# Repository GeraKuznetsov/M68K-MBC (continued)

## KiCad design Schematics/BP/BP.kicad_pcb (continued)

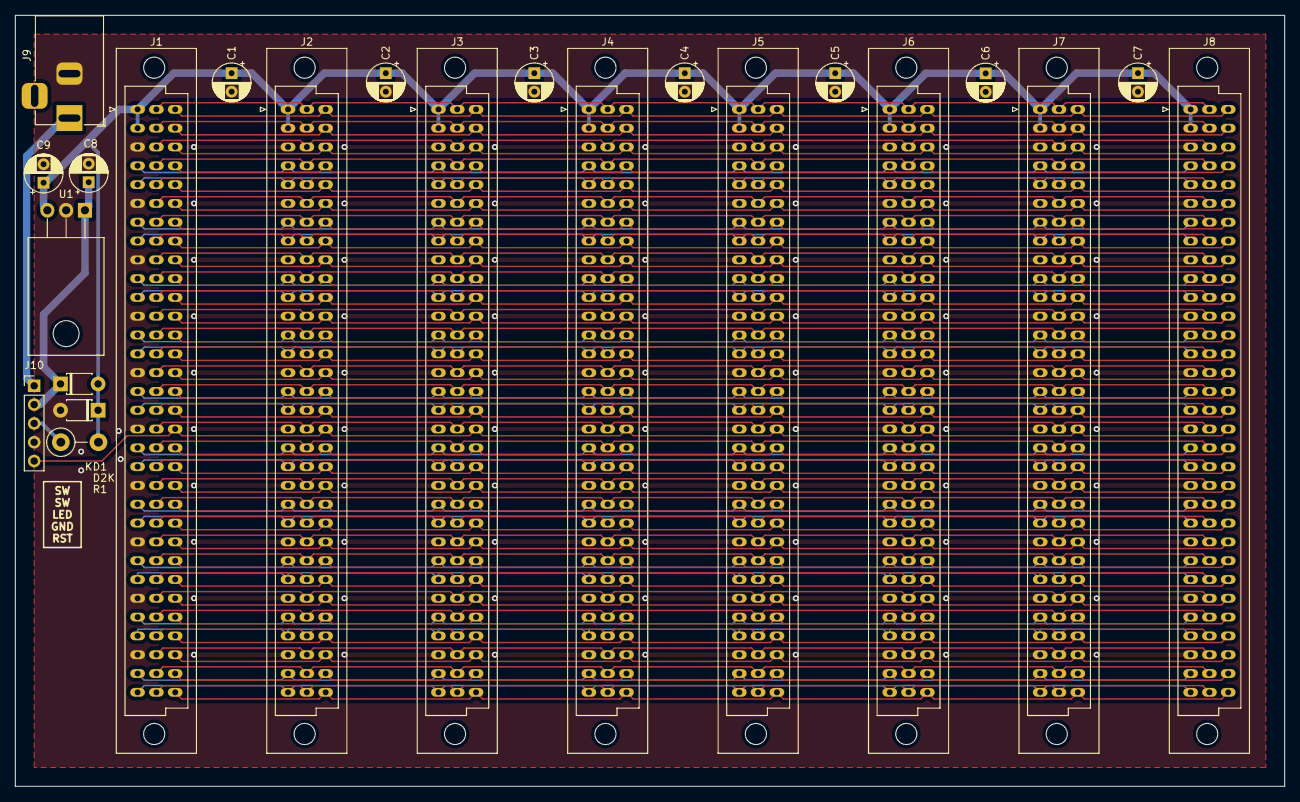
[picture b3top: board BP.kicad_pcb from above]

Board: 2 copper layers, 171.4 x 104.1 mm, 23 parts (0 on the bottom side), 89 nets.

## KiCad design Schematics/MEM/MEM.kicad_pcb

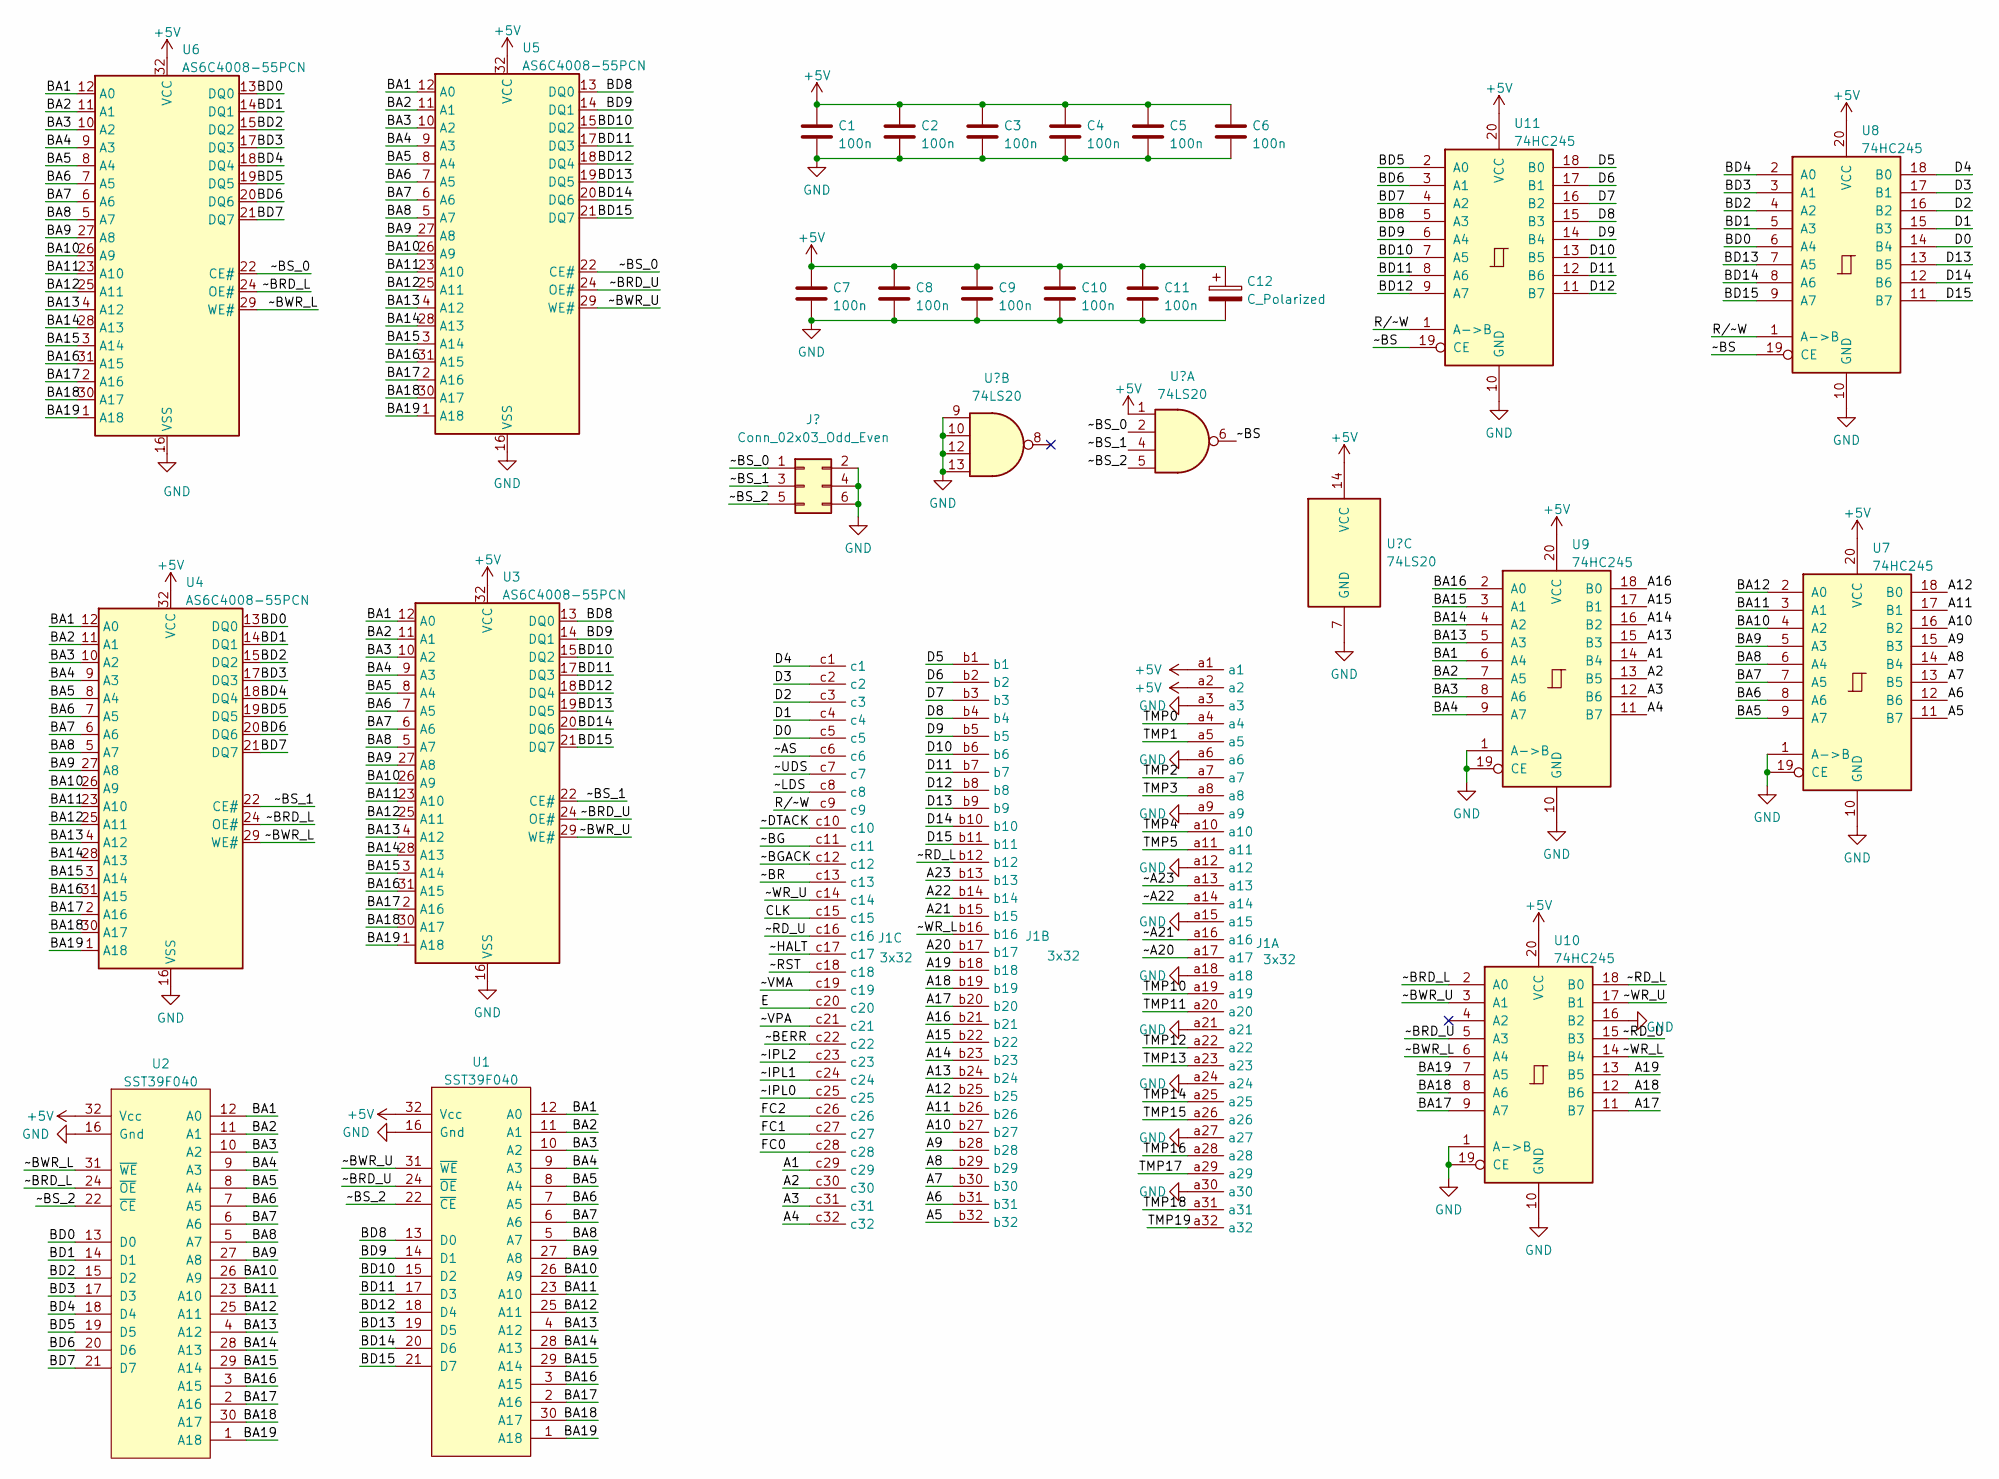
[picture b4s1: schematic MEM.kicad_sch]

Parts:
C1, C2, C3, C4, C5, C6, C7, C8, C9, C10, C11: 100n; DIP-2_200_ELL
C12: C_Polarized; CP_Radial_D4.0mm_P1.50mm
J1: 3x32; DIN41612_R_3x32_Male_Horizontal_THT
U1, U2: SST39F040; DIP-32_600_ELL
U3, U4, U5, U6: AS6C4008-55PCN; DIP-32_600_ELL
U7, U8, U9, U10, U11: 74HC245; DIP-20

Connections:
+5V: C1.1, C2.1, C3.1, C4.1, C5.1, C6.1, C7.1, C8.1, C9.1, C10.1, C11.1, C12.1, J1.a1, J1.a2, U1.32 (Vcc), U2.32 (Vcc), U3.32 (VCC), U4.32 (VCC), U5.32 (VCC), U6.32 (VCC), U7.20 (VCC), U8.20 (VCC), U9.20 (VCC), U10.20 (VCC), U11.20 (VCC)
/A1: J1.c29, U9.14 (B4)
/A2: J1.c30, U9.13 (B5)
/A3: J1.c31, U9.12 (B6)
/A4: J1.c32, U9.11 (B7)
/A5: J1.b32, U7.11 (B7)
/A6: J1.b31, U7.12 (B6)
/A7: J1.b30, U7.13 (B5)
/A8: J1.b29, U7.14 (B4)
/A9: J1.b28, U7.15 (B3)
/A10: J1.b27, U7.16 (B2)
/A11: J1.b26, U7.17 (B1)
/A12: J1.b25, U7.18 (B0)
/A13: J1.b24, U9.15 (B3)
/A14: J1.b23, U9.16 (B2)
/A15: J1.b22, U9.17 (B1)
/A16: J1.b21, U9.18 (B0)
/A17: J1.b20, U10.11 (B7)
/A18: J1.b19, U10.12 (B6)
/A19: J1.b18, U10.13 (B5)
/A20: J1.b17
/A21: J1.b15
/A22: J1.b14
/A23: J1.b13
/BA1: U1.12 (A0), U2.12 (A0), U3.12 (A0), U4.12 (A0), U5.12 (A0), U6.12 (A0), U9.6 (A4)
/BA2: U1.11 (A1), U2.11 (A1), U3.11 (A1), U4.11 (A1), U5.11 (A1), U6.11 (A1), U9.7 (A5)
/BA3: U1.10 (A2), U2.10 (A2), U3.10 (A2), U4.10 (A2), U5.10 (A2), U6.10 (A2), U9.8 (A6)
/BA4: U1.9 (A3), U2.9 (A3), U3.9 (A3), U4.9 (A3), U5.9 (A3), U6.9 (A3), U9.9 (A7)
/BA5: U1.8 (A4), U2.8 (A4), U3.8 (A4), U4.8 (A4), U5.8 (A4), U6.8 (A4), U7.9 (A7)
/BA6: U1.7 (A5), U2.7 (A5), U3.7 (A5), U4.7 (A5), U5.7 (A5), U6.7 (A5), U7.8 (A6)
/BA7: U1.6 (A6), U2.6 (A6), U3.6 (A6), U4.6 (A6), U5.6 (A6), U6.6 (A6), U7.7 (A5)
/BA8: U1.5 (A7), U2.5 (A7), U3.5 (A7), U4.5 (A7), U5.5 (A7), U6.5 (A7), U7.6 (A4)
/BA9: U1.27 (A8), U2.27 (A8), U3.27 (A8), U4.27 (A8), U5.27 (A8), U6.27 (A8), U7.5 (A3)
/BA10: U1.26 (A9), U2.26 (A9), U3.26 (A9), U4.26 (A9), U5.26 (A9), U6.26 (A9), U7.4 (A2)
/BA11: U1.23 (A10), U2.23 (A10), U3.23 (A10), U4.23 (A10), U5.23 (A10), U6.23 (A10), U7.3 (A1)
/BA12: U1.25 (A11), U2.25 (A11), U3.25 (A11), U4.25 (A11), U5.25 (A11), U6.25 (A11), U7.2 (A0)
/BA13: U1.4 (A12), U2.4 (A12), U3.4 (A12), U4.4 (A12), U5.4 (A12), U6.4 (A12), U9.5 (A3)
/BA14: U1.28 (A13), U2.28 (A13), U3.28 (A13), U4.28 (A13), U5.28 (A13), U6.28 (A13), U9.4 (A2)
/BA15: U1.29 (A14), U2.29 (A14), U3.3 (A14), U4.3 (A14), U5.3 (A14), U6.3 (A14), U9.3 (A1)
/BA16: U1.3 (A15), U2.3 (A15), U3.31 (A15), U4.31 (A15), U5.31 (A15), U6.31 (A15), U9.2 (A0)
/BA17: U1.2 (A16), U2.2 (A16), U3.2 (A16), U4.2 (A16), U5.2 (A16), U6.2 (A16), U10.9 (A7)
/BA18: U1.30 (A17), U2.30 (A17), U3.30 (A17), U4.30 (A17), U5.30 (A17), U6.30 (A17), U10.8 (A6)
/BA19: U1.1 (A18), U2.1 (A18), U3.1 (A18), U4.1 (A18), U5.1 (A18), U6.1 (A18), U10.7 (A5)
/BD0: U2.13 (D0), U4.13 (DQ0), U6.13 (DQ0), U8.6 (A4)
/BD1: U2.14 (D1), U4.14 (DQ1), U6.14 (DQ1), U8.5 (A3)
/BD2: U2.15 (D2), U4.15 (DQ2), U6.15 (DQ2), U8.4 (A2)
/BD3: U2.17 (D3), U4.17 (DQ3), U6.17 (DQ3), U8.3 (A1)
/BD4: U2.18 (D4), U4.18 (DQ4), U6.18 (DQ4), U8.2 (A0)
/BD5: U2.19 (D5), U4.19 (DQ5), U6.19 (DQ5), U11.2 (A0)
/BD6: U2.20 (D6), U4.20 (DQ6), U6.20 (DQ6), U11.3 (A1)
/BD7: U2.21 (D7), U4.21 (DQ7), U6.21 (DQ7), U11.4 (A2)
/BD8: U1.13 (D0), U3.13 (DQ0), U5.13 (DQ0), U11.5 (A3)
/BD9: U1.14 (D1), U3.14 (DQ1), U5.14 (DQ1), U11.6 (A4)
/BD10: U1.15 (D2), U3.15 (DQ2), U5.15 (DQ2), U11.7 (A5)
/BD11: U1.17 (D3), U3.17 (DQ3), U5.17 (DQ3), U11.8 (A6)
/BD12: U1.18 (D4), U3.18 (DQ4), U5.18 (DQ4), U11.9 (A7)
/BD13: U1.19 (D5), U3.19 (DQ5), U5.19 (DQ5), U8.7 (A5)
/BD14: U1.20 (D6), U3.20 (DQ6), U5.20 (DQ6), U8.8 (A6)
/BD15: U1.21 (D7), U3.21 (DQ7), U5.21 (DQ7), U8.9 (A7)
/CLK: J1.c15
/D0: J1.c5, U8.14 (B4)
/D1: J1.c4, U8.15 (B3)
/D2: J1.c3, U8.16 (B2)
/D3: J1.c2, U8.17 (B1)
/D4: J1.c1, U8.18 (B0)
/D5: J1.b1, U11.18 (B0)
/D6: J1.b2, U11.17 (B1)
/D7: J1.b3, U11.16 (B2)
/D8: J1.b4, U11.15 (B3)
/D9: J1.b5, U11.14 (B4)
/D10: J1.b6, U11.13 (B5)
/D11: J1.b7, U11.12 (B6)
/D12: J1.b8, U11.11 (B7)
/D13: J1.b9, U8.13 (B5)
/D14: J1.b10, U8.12 (B6)
/D15: J1.b11, U8.11 (B7)
/E: J1.c20
/FC0: J1.c28
/FC1: J1.c27
/FC2: J1.c26
/R/~W: J1.c9, U8.1 (A->B), U11.1 (A->B)
/TMP0: J1.a4
/TMP1: J1.a5
/TMP2: J1.a7
/TMP3: J1.a8
/TMP4: J1.a10
/TMP5: J1.a11
/TMP10: J1.a19
/TMP11: J1.a20
/TMP12: J1.a22
/TMP13: J1.a23
/TMP14: J1.a25
/TMP15: J1.a26
/TMP16: J1.a28
/TMP17: J1.a29
/TMP18: J1.a31
/TMP19: J1.a32
/~A20: J1.a17
/~A21: J1.a16
/~A22: J1.a14
/~A23: J1.a13
/~AS: J1.c6
/~BERR: J1.c22
/~BG: J1.c11
/~BGACK: J1.c12
/~BR: J1.c13
/~BRD_L: U2.24 (~OE), U4.24 (OE#), U6.24 (OE#), U10.2 (A0)
/~BRD_U: U1.24 (~OE), U3.24 (OE#), U5.24 (OE#), U10.5 (A3)
/~BS: U8.19 (CE), U11.19 (CE)
/~BS_0: U5.22 (CE#), U6.22 (CE#)
/~BS_1: U3.22 (CE#), U4.22 (CE#)
/~BS_2: U1.22 (~CE), U2.22 (~CE)
/~BWR_L: U2.31 (~WE), U4.29 (WE#), U6.29 (WE#), U10.6 (A4)
/~BWR_U: U1.31 (~WE), U3.29 (WE#), U5.29 (WE#), U10.3 (A1)
/~DTACK: J1.c10
/~HALT: J1.c17
/~IPL0: J1.c25
/~IPL1: J1.c24
/~IPL2: J1.c23
/~LDS: J1.c8
/~RD_L: J1.b12, U10.18 (B0)
/~RD_U: J1.c16, U10.15 (B3)
/~RST: J1.c18
/~UDS: J1.c7
/~VMA: J1.c19
/~VPA: J1.c21
/~WR_L: J1.b16, U10.14 (B4)
/~WR_U: J1.c14, U10.17 (B1)
GND: C1.2, C2.2, C3.2, C4.2, C5.2, C6.2, C7.2, C8.2, C9.2, C10.2, C11.2, C12.2, J1.a3, J1.a6, J1.a9, J1.a12, J1.a15, J1.a18, J1.a21, J1.a24, J1.a27, J1.a30, U1.16 (Gnd), U2.16 (Gnd), U3.16 (VSS), U4.16 (VSS), U5.16 (VSS), U6.16 (VSS), U7.1 (A->B), U7.10 (GND), U7.19 (CE), U8.10 (GND), U9.1 (A->B), U9.10 (GND), U9.19 (CE), U10.1 (A->B), U10.10 (GND), U10.16 (B2), U10.19 (CE), U11.10 (GND)

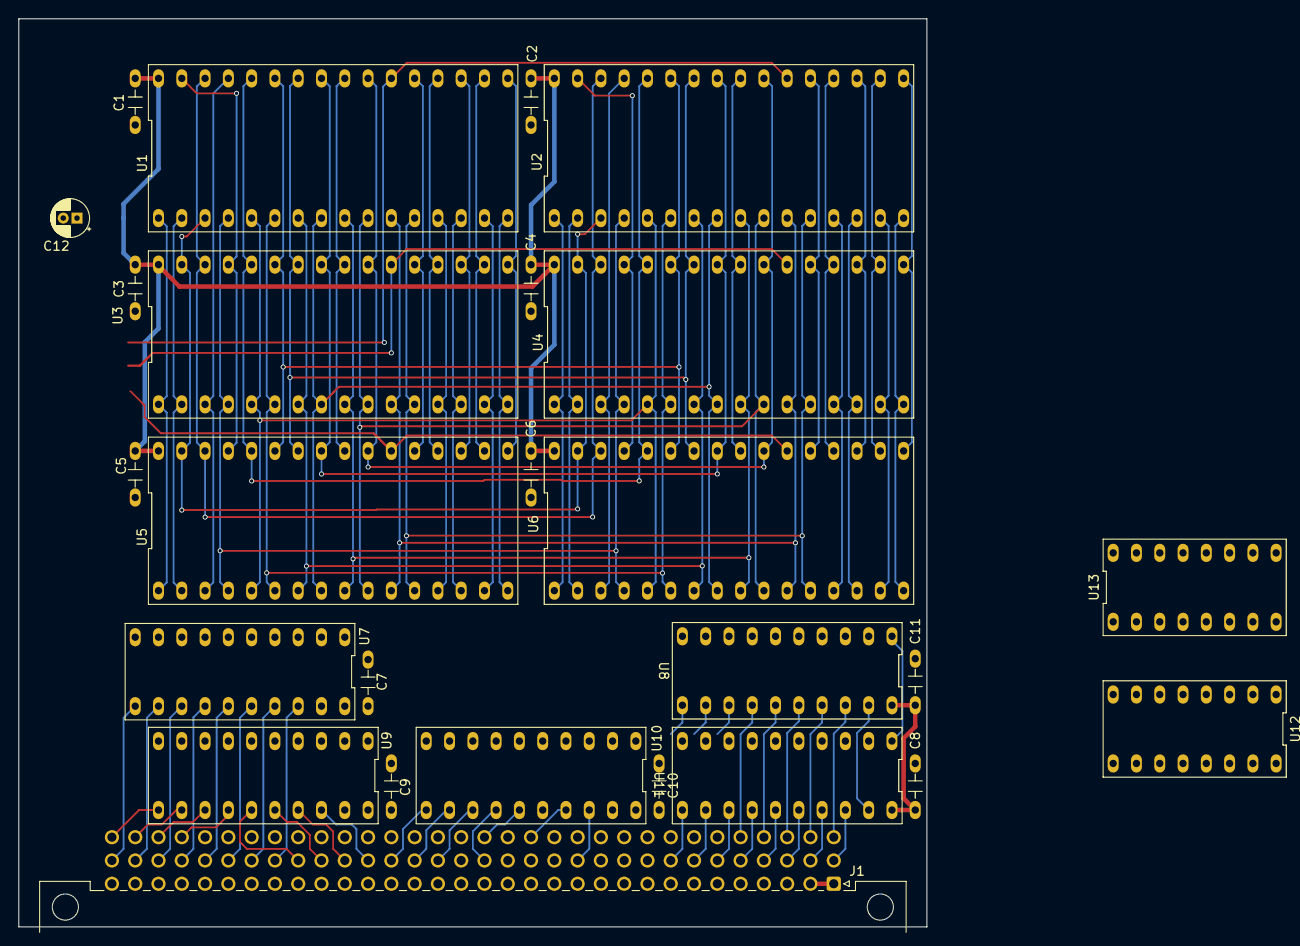
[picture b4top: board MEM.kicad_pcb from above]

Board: 4 copper layers, 99.1 x 99.1 mm, 26 parts (0 on the bottom side), 85 nets.

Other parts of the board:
U12: 74LS85; DIP-16
U13: 74LS138; DIP-16

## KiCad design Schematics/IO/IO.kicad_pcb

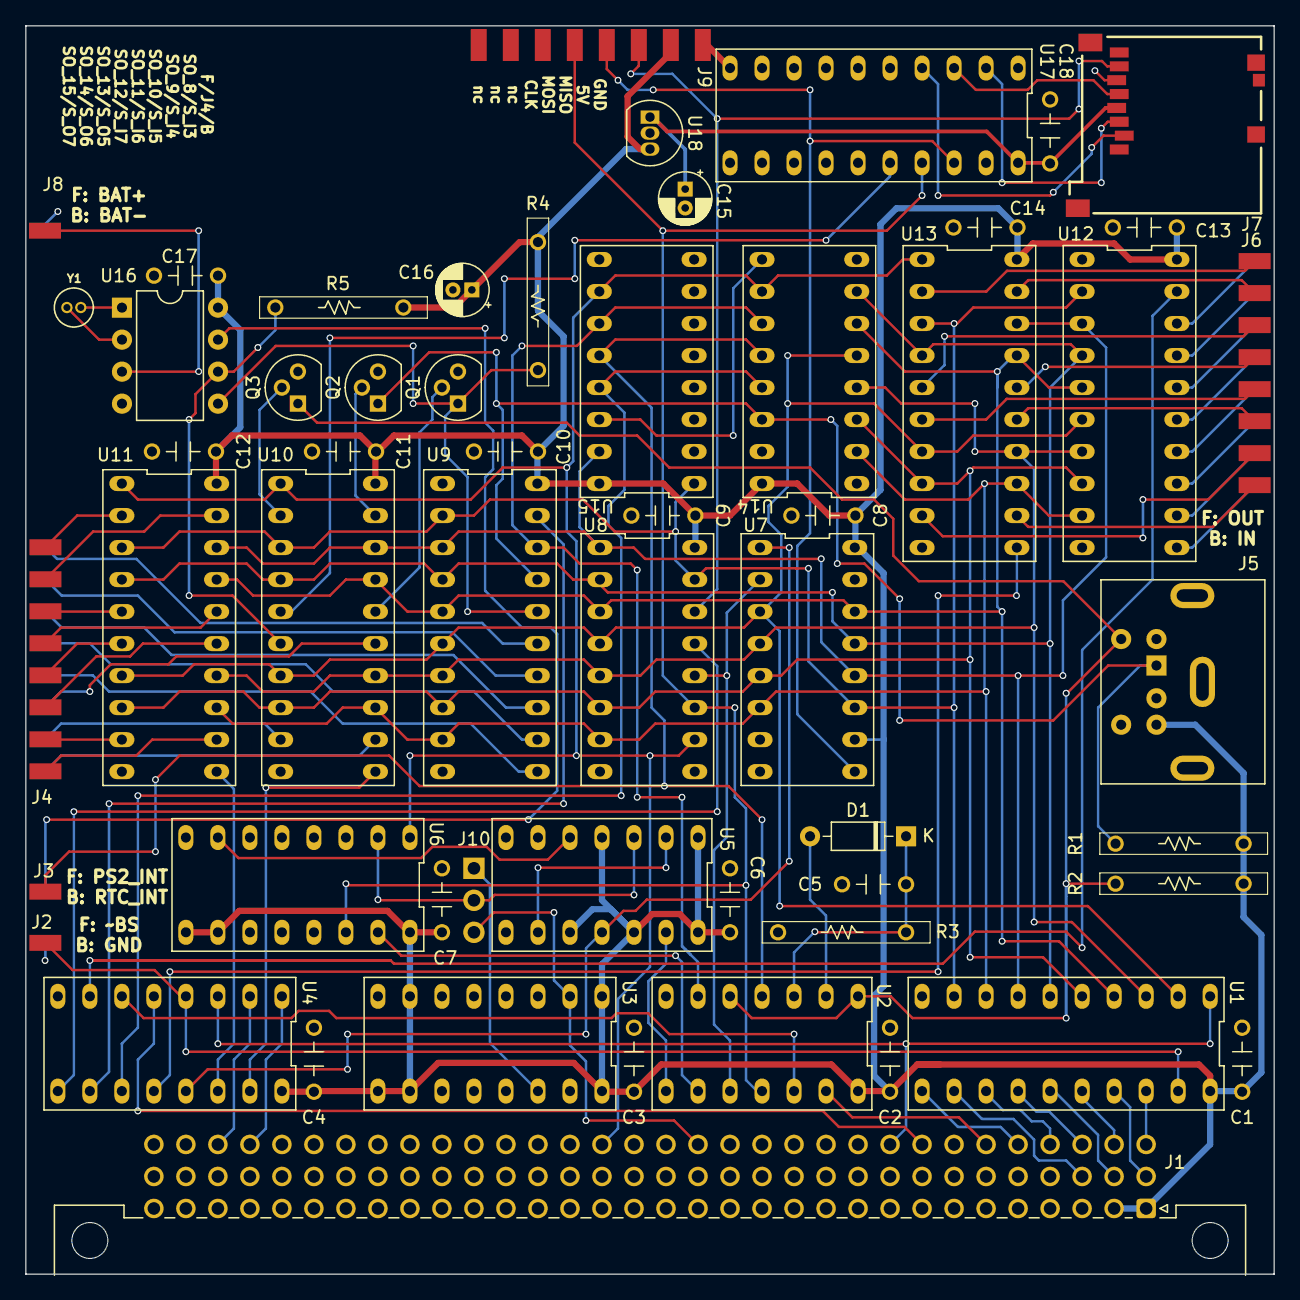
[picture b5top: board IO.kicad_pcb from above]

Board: 4 copper layers, 99.1 x 99.1 mm, 56 parts (0 on the bottom side), 98 nets.

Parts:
C1, C2, C3, C4, C6, C7, C8, C9, C10, C11, C12, C13, C14, C17, C18: 100n; DIP-2_200_ELL
C5: 100nF; DIP-2_200_ELL
C15, C16: C_Polarized; CP_Radial_D4.0mm_P1.50mm
D1: D; D_DO-35_SOD27_P7.62mm_Horizontal
J1: 3x32; DIN41612_R_3x32_Male_Horizontal_THT
J2, J3, J8: 2x01; 2x01 finger
J4: Conn_02x08_Top_Bottom; 2x08 finger
J5: Mini-DIN-6; din
J6: 02x08; 2x08 finger
J7: Micro_SD_Card_Det; sd
J9: 2x08; 2x08 finger
J10: 1x03; PinHeader_1x03_P2.54mm_Vertical
Q1, Q2, Q3: Q_NMOS_DGS; TO-92
R1, R2, R3: 1K; res
R4, R5: R; res
U1, U9, U12: 74HC245; DIP-20
U2: 74HC14; DIP-14
U3, U6: 74LS161; DIP-16
U4: 74LS138; DIP-16
U5: 74HC74; DIP-14
U7: 74HC165; DIP-16
U8, U14, U15: 74HC595; DIP-16
U10, U11, U13: 74HC273; DIP-20
U16: DS1307+; DIP-8_W7.62mm
U17: 74LVC245; DIP-20
U18: LP2950-3.3_TO92; TO-92_Inline
Y1: 32768hz; XTAL_ECS-.327-12.5-8X-C

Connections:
+3V3: C15.1, C18.1, J7.4 (VDD), U17.20 (VCC), U18.1 (VO)
+5V: C1.1, C2.1, C3.1, C4.1, C6.1, C7.1, C8.1, C9.1, C10.1, C11.1, C12.1, C13.1, C14.1, C16.1, C17.1, J1.a1, J1.a2, J5.4, J9.2, R1.1, R2.1, R4.1, R5.1, U1.20 (VCC), U2.14 (VCC), U3.1 (~MR), U3.7 (CEP), U3.9 (~PE), U3.10 (CET), U3.16 (VCC), U4.16 (VCC), U5.1 (~R), U5.4 (~S), U5.10 (~S), U5.12 (D), U5.14 (VCC), U6.9 (~PE), U6.10 (CET), U6.16 (VCC), U7.10 (DS), U7.16 (VCC), U8.16 (VCC), U9.20 (VCC), U10.20 (VCC), U11.20 (VCC), U12.20 (VCC), U13.20 (VCC), U14.16 (VCC), U15.16 (VCC), U16.8 (VCC), U18.3 (VI)
/A1: J1.c29, U4.1 (A0)
/A2: J1.c30, U4.2 (A1)
/BD0: U1.9 (A7), U7.11 (D0), U8.15 (QA), U9.2 (A0), U10.3 (D0), U11.3 (D0), U12.2 (A0), U13.3 (D0), U15.1 (QB)
/BD1: U1.7 (A5), U7.12 (D1), U8.1 (QB), U9.3 (A1), U10.18 (D7), U11.18 (D7), U12.3 (A1), U13.18 (D7), U15.15 (QA)
/BD2: U1.6 (A4), U7.13 (D2), U8.2 (QC), U9.4 (A2), U10.4 (D1), U11.4 (D1), U12.4 (A2), U13.4 (D1), U14.7 (QH)
/BD3: U1.4 (A2), U7.14 (D3), U8.3 (QD), U9.5 (A3), U10.17 (D6), U11.17 (D6), U12.5 (A3), U13.17 (D6), U14.6 (QG)
/BD4: U1.2 (A0), U7.3 (D4), U8.4 (QE), U9.6 (A4), U10.7 (D2), U11.7 (D2), U12.6 (A4), U13.7 (D2), U14.5 (QF)
/BD5: U1.3 (A1), U7.4 (D5), U8.5 (QF), U9.7 (A5), U10.14 (D5), U11.14 (D5), U12.7 (A5), U13.14 (D5), U14.4 (QE)
/BD6: U1.5 (A3), U7.5 (D6), U8.6 (QG), U9.8 (A6), U10.8 (D3), U11.8 (D3), U12.8 (A6), U13.8 (D3), U14.3 (QD)
/BD7: U1.8 (A6), U7.6 (D7), U8.7 (QH), U9.9 (A7), U10.13 (D4), U11.13 (D4), U12.9 (A7), U13.13 (D4), U14.2 (QC)
/CLK: J1.c15, J10.3, U3.2 (CP)
/CLK2: J10.1, U3.14 (Q0)
/D0: J1.c5, U1.11 (B7)
/D1: J1.c4, U1.13 (B5)
/D2: J1.c3, U1.14 (B4)
/D3: J1.c2, U1.16 (B2)
/D4: J1.c1, U1.18 (B0)
/D5: J1.b1, U1.17 (B1)
/D6: J1.b2, U1.15 (B3)
/D7: J1.b3, U1.12 (B6)
/IO_RD_0: U4.11 (O4), U14.13 (~OE), U15.13 (~OE)
/IO_RD_1: U4.10 (O5), U9.19 (CE)
/IO_RD_2: U4.9 (O6), U8.13 (~OE)
/IO_RD_3: U4.7 (O7), U12.19 (CE)
/IO_WR_0: U4.15 (O0), U10.11 (Cp)
/IO_WR_1: U4.14 (O1), U11.11 (Cp)
/IO_WR_2: U4.13 (O2), U5.11 (C), U7.1 (~PL)
/IO_WR_3: U4.12 (O3), U13.11 (Cp)
/OD0: J6.1, U13.2 (Q0)
/OD1: J6.2, U13.19 (Q7)
/OD2: J6.3, U13.5 (Q1)
/OD3: J6.4, U13.16 (Q6)
/OD4: J6.5, U13.6 (Q2)
/OD5: J6.6, U13.15 (Q5)
/OD6: J6.7, U13.9 (Q3)
/OD7: J6.8, U13.12 (Q4)
/PS2_CLOCK: Q3.2 (G), U10.2 (Q0)
/PS2_DATA: Q2.2 (G), U10.19 (Q7)
/PS2_INT: J3.1, U2.4, U14.12 (RCLK), U15.12 (RCLK)
/RTC_INT: J3.2, U16.7 (SQW/OUT)
/R/~W: J1.c9, U1.1 (A->B), U4.3 (A2)
/SCL: R5.2, U10.6 (Q2), U16.6 (SCL)
/SDA: Q1.1 (D), R4.2, U9.16 (B2), U16.5 (SDA)
/SD_CLK: J7.5 (CLK), U17.3 (A1)
/SD_CS0: J7.2 (DAT3/CD), U17.4 (A2)
/SD_D1: J7.3 (CMD), U17.2 (A0)
/SD_DO: J7.7 (DAT0), J9.3, U8.14 (SER)
/SPI_CE0: U10.5 (Q1), U17.16 (B2)
/SPI_CLK: J9.5, U2.11, U6.14 (Q0), U8.11 (SRCLK), U17.17 (B1)
/SPI_MOSI: J9.4, U7.9 (Q7), U17.18 (B0)
/SYS_IN_3: J4.16, U9.15 (B3)
/SYS_IN_4: J4.15, U9.14 (B4)
/SYS_IN_5: J4.14, U9.13 (B5)
/SYS_IN_6: J4.13, U9.12 (B6)
/SYS_IN_7: J4.12, U9.11 (B7)
/SYS_OUT_5: J4.11, U10.15 (Q5)
/SYS_OUT_6: J4.10, U10.9 (Q3)
/SYS_OUT_7: J4.9, U10.12 (Q4)
/SYS_OUT_8: J4.8, U11.2 (Q0)
/SYS_OUT_9: J4.7, U11.19 (Q7)
/SYS_OUT_10: J4.6, U11.5 (Q1)
/SYS_OUT_11: J4.5, U11.16 (Q6)
/SYS_OUT_12: J4.4, U11.6 (Q2)
/SYS_OUT_13: J4.3, U11.15 (Q5)
/SYS_OUT_14: J4.2, U11.9 (Q3)
/SYS_OUT_15: J4.1, U11.12 (Q4)
/~AS: J1.c6, U2.13
/~BS: J2.1, U1.19 (CE), U4.4 (E1)
/~LDS: J1.c8, U4.5 (E2)
/~RST: J1.c18, U6.1 (~MR), U8.10 (~SRCLR), U10.1 (~Mr), U11.1 (~Mr), U13.1 (~Mr), U14.10 (~SRCLR), U15.10 (~SRCLR)
/~SPI_CLK: U2.10, U7.2 (CP), U8.12 (RCLK)
GND: C1.2, C2.2, C3.2, C4.2, C5.2, C6.2, C7.2, C8.2, C9.2, C10.2, C11.2, C12.2, C13.2, C14.2, C15.2, C16.2, C17.2, C18.2, J1.a3, J1.a6, J1.a9, J1.a12, J1.a15, J1.a18, J1.a21, J1.a24, J1.a27, J1.a30, J2.2, J5.3, J7.6 (VSS), J8.2, J9.1, Q1.3 (S), Q2.3 (S), Q3.3 (S), R3.2, U1.10 (GND), U2.7 (GND), U3.3 (D0), U3.4 (D1), U3.5 (D2), U3.6 (D3), U3.8 (GND), U4.8 (GND), U5.7 (GND), U6.3 (D0), U6.4 (D1), U6.5 (D2), U6.6 (D3), U6.8 (GND), U7.8 (GND), U7.15 (~CE), U8.8 (GND), U9.1 (A->B), U9.10 (GND), U10.10 (GND), U11.10 (GND), U12.1 (A->B), U12.10 (GND), U13.10 (GND), U14.8 (GND), U15.8 (GND), U16.4 (GND), U17.1 (A->B), U17.10 (GND), U17.19 (CE), U18.2 (GND)
unnamed: C5.1, D1.1 (K), R3.1, U2.3
unnamed: D1.2 (A), U2.2
unnamed: J5.1, Q2.1 (D), R1.2, U9.17 (B1), U14.14 (SER)
unnamed: J5.5, Q3.1 (D), R2.2, U2.1, U2.5
unnamed: J6.9, U12.18 (B0)
unnamed: J6.10, U12.17 (B1)
unnamed: J6.11, U12.16 (B2)
unnamed: J6.12, U12.15 (B3)
unnamed: J6.13, U12.14 (B4)
unnamed: J6.14, U12.13 (B5)
unnamed: J6.15, U12.12 (B6)
unnamed: J6.16, U12.11 (B7)
unnamed: J8.1, U16.3 (VBAT)
unnamed: J10.2, U5.3 (C), U6.2 (CP)
unnamed: Q1.2 (G), U10.16 (Q6)
unnamed: U2.8, U5.13 (~R)
unnamed: U2.9, U6.15 (TC)
unnamed: U2.12, U4.6 (E3)
unnamed: U5.2 (D), U5.9 (Q)
unnamed: U5.5 (Q), U6.7 (CEP)
unnamed: U14.9 (QH'), U15.14 (SER)
unnamed: U2.6, U9.18 (B0), U14.11 (SRCLK), U15.11 (SRCLK)
unnamed: U16.1 (X1), Y1.2
unnamed: U16.2 (X2), Y1.1
